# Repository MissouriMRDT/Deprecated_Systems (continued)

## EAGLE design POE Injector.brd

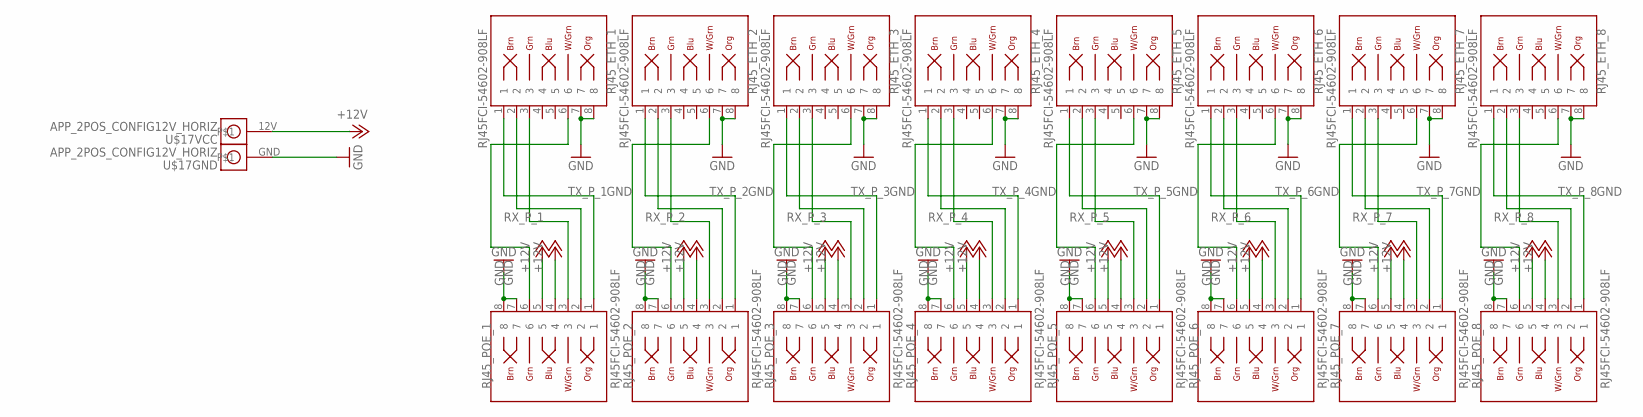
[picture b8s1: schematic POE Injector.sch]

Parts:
RJ45_ETH_1, RJ45_ETH_2, RJ45_ETH_3, RJ45_ETH_4, RJ45_ETH_5, RJ45_ETH_6, RJ45_ETH_7, RJ45_ETH_8, RJ45_POE_1, RJ45_POE_2, RJ45_POE_3, RJ45_POE_4, RJ45_POE_5, RJ45_POE_6, RJ45_POE_7, RJ45_POE_8: RJ45FCI-54602-908LF; FCI-54602-908LF
U$17: APP_2POS_CONFIG12V_HORIZ; APP45_12V_HORIZ_CONFIG

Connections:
+12V: RJ45_POE_1.4, RJ45_POE_1.5, RJ45_POE_2.4, RJ45_POE_2.5, RJ45_POE_3.4, RJ45_POE_3.5, RJ45_POE_4.4, RJ45_POE_4.5, RJ45_POE_5.4, RJ45_POE_5.5, RJ45_POE_6.4, RJ45_POE_6.5, RJ45_POE_7.4, RJ45_POE_7.5, RJ45_POE_8.4, RJ45_POE_8.5, U$17.12V
GND: RJ45_ETH_1.7, RJ45_ETH_1.8, RJ45_ETH_2.7, RJ45_ETH_2.8, RJ45_ETH_3.7, RJ45_ETH_3.8, RJ45_ETH_4.7, RJ45_ETH_4.8, RJ45_ETH_5.7, RJ45_ETH_5.8, RJ45_ETH_6.7, RJ45_ETH_6.8, RJ45_ETH_7.7, RJ45_ETH_7.8, RJ45_ETH_8.7, RJ45_ETH_8.8, RJ45_POE_1.7, RJ45_POE_1.8, RJ45_POE_2.7, RJ45_POE_2.8, RJ45_POE_3.7, RJ45_POE_3.8, RJ45_POE_4.7, RJ45_POE_4.8, RJ45_POE_5.7, RJ45_POE_5.8, RJ45_POE_6.7, RJ45_POE_6.8, RJ45_POE_7.7, RJ45_POE_7.8, RJ45_POE_8.7, RJ45_POE_8.8, U$17.GND
RX_N_1: RJ45_ETH_1.6, RJ45_POE_1.6
RX_N_2: RJ45_ETH_2.6, RJ45_POE_2.6
RX_N_3: RJ45_ETH_3.6, RJ45_POE_3.6
RX_N_4: RJ45_ETH_4.6, RJ45_POE_4.6
RX_N_5: RJ45_ETH_5.6, RJ45_POE_5.6
RX_N_6: RJ45_ETH_6.6, RJ45_POE_6.6
RX_N_7: RJ45_ETH_7.6, RJ45_POE_7.6
RX_N_8: RJ45_ETH_8.6, RJ45_POE_8.6
RX_P_1: RJ45_ETH_1.3, RJ45_POE_1.3
RX_P_2: RJ45_ETH_2.3, RJ45_POE_2.3
RX_P_3: RJ45_ETH_3.3, RJ45_POE_3.3
RX_P_4: RJ45_ETH_4.3, RJ45_POE_4.3
RX_P_5: RJ45_ETH_5.3, RJ45_POE_5.3
RX_P_6: RJ45_ETH_6.3, RJ45_POE_6.3
RX_P_7: RJ45_ETH_7.3, RJ45_POE_7.3
RX_P_8: RJ45_ETH_8.3, RJ45_POE_8.3
TX_N_1: RJ45_ETH_1.2, RJ45_POE_1.2
TX_N_2: RJ45_ETH_2.2, RJ45_POE_2.2
TX_N_3: RJ45_ETH_3.2, RJ45_POE_3.2
TX_N_4: RJ45_ETH_4.2, RJ45_POE_4.2
TX_N_5: RJ45_ETH_5.2, RJ45_POE_5.2
TX_N_6: RJ45_ETH_6.2, RJ45_POE_6.2
TX_N_7: RJ45_ETH_7.2, RJ45_POE_7.2
TX_N_8: RJ45_ETH_8.2, RJ45_POE_8.2
TX_P_1: RJ45_ETH_1.1, RJ45_POE_1.1
TX_P_2: RJ45_ETH_2.1, RJ45_POE_2.1
TX_P_3: RJ45_ETH_3.1, RJ45_POE_3.1
TX_P_4: RJ45_ETH_4.1, RJ45_POE_4.1
TX_P_5: RJ45_ETH_5.1, RJ45_POE_5.1
TX_P_6: RJ45_ETH_6.1, RJ45_POE_6.1
TX_P_7: RJ45_ETH_7.1, RJ45_POE_7.1
TX_P_8: RJ45_ETH_8.1, RJ45_POE_8.1

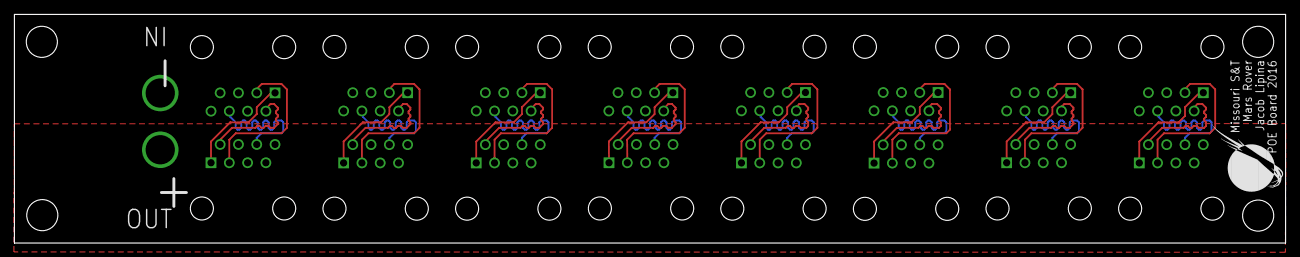
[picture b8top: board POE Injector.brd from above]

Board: 2 copper layers, 176.5 x 31.8 mm, 18 parts (0 on the bottom side), 34 nets.

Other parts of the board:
U$1: MRDT_LOGO

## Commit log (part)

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2016-10-25 Updated Gitignore and removed stray file
2016-10-25 Finished routing Dropbay Connectors
2016-10-27 Code standard changes, more comments.
2016-10-28 Implemented read and graph of spectrometer data.
2016-11-03 Updated template area to latest template
2016-11-04 Added 12V Actuation to run servos
2016-11-04 Updated Donation Address
2016-11-05 Added LSM9DS1 IMU to MRDT-Sensors
2016-11-06 Completed Rev 1 of Science Board
    Added second sensor board and completed board design.
2016-11-06 Rounded corners of board
2016-11-06 Edits after review
    Complete rearrangement of board to put circuitry under Tiva, with
    horizontal connectors. Changed layout of photodiode amplifier circuit to
    reduce noise. Added mounting holes and rounded corners. Replaced I2C
    level shifter IC. tided up traces and component names.
2016-11-07 Stitched GNDs better
2016-11-07 Added SL02-Horiz
2016-11-08 Changed drill size for Vias to 12mil
2016-11-08 Add SL5 connectors for motors, passthrough serial data
    Motors get independent control in normal mode, tank steer (left together, right together) in failover mode
2016-12-03 Converted DropBay control to use an array of Servos
2016-12-16 update gitignore
2016-12-16 Weather and Soil Sensor boards
2017-01-05 Add tab to display pictures
2017-01-07 Added name to test point package
2017-01-08 Finished routing and labeled board
2017-01-10 Updated LXDC2HN
2017-01-12 Completed board review #1 revisions
2017-01-12 Board Review revisions completed
2017-01-21 Add images to directory and add functionality to import png images
2017-01-27 Test app functionality for science board
    Test app to control flap, laser, carousel, other functions. in
    development
2017-02-02 Create show picture funciton
2017-02-03 Updated to match ordered Ext Controls board
    Made Vias Smaller
    Moved Ethernet Circuitry lower
    Added Actuation Bus
    Updated Libraries
    Rounded Board Corners
2017-02-03 Added Max4312 chip to schematic
2017-02-03 Added Molex BNC
2017-02-04 added opamp
2017-02-04 Testing science board things
    minor changes
2017-02-10 Remove arm.h, update science board code
2017-02-15 Added dynamixel connector and serial line
2017-02-25 Orgainize Test Sketches into one folder
2017-03-01 Tested and fixed these sketches.
    I have seen these work!
2017-03-02 added arm board V2's 3.3V lin reg
2017-03-04 Added more comments to improve readability
    Added comments for functions, control blocks, and the mail execution
    loop, Added TODO: coments
2017-03-09 Traces for Dynamixels and extra PWMs
2017-03-14 added arm board inductor
2017-03-15 Make Cmd ID enum, added millis sensor delay
    Enumerated command Data for science commands, added delay between sensor
    reads, initialized all sensors to off
2017-03-18 Switch main motor driver, fixed issues with 3V3
2017-03-20 Integrated weather sensor board, started soil sensor integration, changed spectrometer motor driver
2017-03-21 Quick + basic RPi hat
2017-03-22 some changes from board review
    > remove diodes for LEDs
    > space out FETs
    > separate grounds for FETs
    > Move vias out from under FETs
2017-03-22 Removed unnecessary 3v3 net and swapped header with eagle standard part
2017-03-23 made changes related to board review
2017-03-23 Widened board and spaced out connectors
2017-03-23 Changes to Arm board
    Fixed text, added divider resistors to sensors, added power LED, rearranged schematic slightly
2017-03-23 Added the actual program file for arm
    Added the actual science arm main program
2017-03-23 adjustable regulator for laser
    BA00DD0WHFP-TR
2017-03-23 changed tiva pins for soil sensors
2017-03-23 Rerouted 12V_ACT for better planes
2017-03-23 ONE MORE I SWEAR
    fixed airwire.
2017-03-23 Updated Revision text
2017-03-23 finished gimbal breakout
    added mounting holes
    labeled board
    fixed traces
2017-04-02 Debug Work - flap and serial comm
    switched flap open and close angles
    tweaked flap open and close angles
    commented out annoying print messages
2017-04-03 Basic functionality for soil temperature and humidity readings as well as spectrometer are implemented and elementary test confirmed.
2017-04-04 Four pictures input as a 2x2 grid on the picture tab.
2017-04-05 Small changes
2017-04-05 Dynamixel LED blinking for debugging (untested)
2017-04-06 Modify to account for Gryphon graphs (Gryphs? Graphon?). Untested with real data. Add QOL picture features (fullscreen, browsed file input)
2017-04-06 Both gimbals fully functional
2017-04-09 changes due to new science board
    testing for carousel, new pins
2017-04-13 add this file
    add this file
2017-04-22 fixed main gimabal serial, and added untested menu functionality
2017-04-22 Code Review 2, Updated TODOs
    Second Code Review, 4/22/17, Updated TODOs in arm board and science
    board
2017-04-23 adding sensor code to science and sci-arm
    copied code from sensor test sketches into science.ino and arm.ino/arm.h
    init all sensor pins for input
    set sensor pins in header file
2017-04-28 added sensor functions to arm board and clean up science.ino
    add ability for continuous data to science arm board, clean up
    code/better organize it ☺
2017-04-29 added AZ1117EH-5.0
2017-05-09 Defined Pins, Added Config, Matched CommandIDs
    Defined Pins in header files, Added Configuration File for Future Sensor
    Calibration, Matched Command IDs to the current RED version
2017-05-15 TCP for phot data and data ids for arm
    :+1:
2017-05-23 updated parameters and tested sample data
2017-05-23 Added Drop Bay close capability
2017-05-24 Added end of year stuff and fixed change to sensor names
2017-05-25 updated carabiner code
2017-05-26 Started implementing new data processing method
2017-05-26 plotted spectrometer data
2017-05-26 Corrected diode switch
2017-05-27 Fixed carabiner value check
2017-09-12 Pre-repo progress commit
2017-09-14 Spectra should be working properly.
2017-09-15 Requests for weather, soil, spectrometer, all working.
2017-09-23 Add functionality to insert raw spectra
2017-09-23 Subscribe to all IP addresses from our configuration file
2017-09-24 Finished adding comps and changing labels
    All components that will be on gimbal pwer board have been added and wires have been renamed to match gimbal design. Last schematic change to make is label header pins.
2017-09-28 Upgrade from PyQt4 to PyQt5.
2017-09-29 Added the 74LVC 2-1 Demux
    Added 2-1 demux and fixed some of the packages added in previous commit
    (added pin 1 markers).
2017-10-01 Added grounds for the acs781
2017-10-01 specroprocessing
2017-10-01 Header pins to control card named
    All traces that will go to control card have been named on a header pin and can be rearanged for more convienent layout. Power indication simplified.
2017-10-01 C2000 Launchpad Schematic and Board
    C2000 CAD files
2017-10-08 Deleted accidental Eagle files
2017-10-13 The motor controller driver for powerboard is ready for rev 1
    This is the complete powerboard design based off of what was decided at the Gimbal meetings. The actual schematic for the board is simply 1A.sch and the board design is 1A.brd I did change some pin a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
2017-10-15 Capacitor fixed
    Hole outline was on the wrong layer
2017-10-16 Started deleting unnecessary hardware on F28069M
    Matched pinout from 28027F with pins on 28069M and deleted all remeaining unnecessary pins. Deleted the debugging and flashing hardware. Decided to delete all muxes and logic gates because we believe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
2017-10-19 Added F28069M Microcontroller
    Took Ti's schematic and board and deleted unecessary functionality. We are using what remains as an integrated version of the F28069M.
2017-10-19 Deleted lock
    My eagle keeps adding locks to my files, which may prevent other people from opening the files, I'm not really sure.
2017-10-20 Named GPIO and ADC pins on F28069M
    Still need to sort out errors identified by ERC.
2017-10-21 Removed Temp Files
2017-10-21 Rearanged Board and rounded edges
    Put Anderson Connectors in correct places as well as rewired the whole board. I then rounded the corners of the board and put wholes in the board so we could properly mount it. Eagle would not allow 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
2017-10-28 Initialize subscriber array with null ip addresses / data id's
2017-10-29 Got width standardized
    Every wire and polygon now has a width of 16 mil
2017-10-29 Fets are now foldable
    Had to move caps around to get fets ample space to be able to be folded down under the board. Approximately 20mm of space. Will still need changes as top chip is finished. Power now has to round seve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
2017-10-30 layout for control card created
    Placed large components, now placing placing passive components individually and routing
2017-11-02 Quick Routing and Labeling Fix
    Straigtenned header names and made sure polygons stretched to same length on board.
2017-11-04 Added Silkscreen and Bill of Materials
    Bill of materials is now added and can be changed as time goes on. All objects on board have been smashed and names are fairly visible. Some areas around phase C are hard to read due to spacing. Silk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
2017-11-04 Fixed some spacing issues
    Moved a wire and straigtenned some polygons for a tighter board.
2017-11-04 more finishing touches.
2017-11-06 Deleted brd and edited schematic
2017-11-07 finsihed simple connections. All devices are on board. Still a lot of pins on header that need to be connected to microprocessor. A lot of them cross. Not sure if possible without vias.
2017-11-08 All the routing is finished. It needs some serious cleaning up and there are most likely mistakes.
2017-11-14 Added BOM and order sheet, modified Board Layout
2017-11-14 Updated Gerber Files; Final changes to board design
2017-11-16 Drill Board: Starting from a clean slate (power and filtering only)
2017-12-02 Fixed formatting for google doc initial push.
2017-12-02 Made data, data_byte_count, and data_id zero in Rovecomm_recieve. UNTESTED
2017-12-09 Fixed some naming errors and moved all funcions out of _init_
2017-12-09 Make Readme formatting nicer
2017-12-30 Added SL connectors & MAX232, added Andrew's JTAG connector
    Added SL connectors from gimbal power board and added connections to BOOSTXL header / MAX232. Same implementation as gimbal power board.
2018-01-01 Improved Interface Documentation
2018-01-04 Finished Routing Board
    Board is finished with routing, however it needs silkscreen to be done. Silk screen will be completed at a later date. There is one unbroken ground plain. Top plain is fairly broken as a ground plane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
2018-01-14 Remved unnecesary files
    BOM and connection information moved to Google Drive under 2018-->Rovecore Electrical-->Programmer Board
2018-01-15 Updated silkscreen and moved reset switch
    The board was shrunken for better fitting with boards that this card will be compatible with. Reset switch was moved to accomodate this. The Jtag connector routing was fixed due to a placement error.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
2018-01-20 Did a little comment reformatting
2018-01-20 first training
2018-01-23 Routing and Silkscreen Update
    New routes were made and Silkscreen changes were made. SL connectors are now labelled and arrows indicate direction of headers.
2018-01-24 Updated schematic and board for final board review
    Changed oscilator for ATMEGA
    changed power to ATMEGA to 3.3V
    Cleaned up position and traces
    Added mounting holes
    Added signature and board data
2018-01-24 Removed redundant SL connector, restructured right side of board and reduced board size
2018-01-25 Rev 3 Gerbs created
2018-01-25 Control Card Routing Update
    Connected VCC to all necessary parts.
2018-01-27 Routing Update
    Board's routing was completely redone and is much more efficient with plenty of vias connecting the ground planes.
2018-01-28 Small Via changes
2018-01-31 Created Gerbs
2018-02-04 Updated read me
2018-02-04 readme
2018-02-04 Master read me
2018-02-04 Revert "Added JLCPCB CAM files"
    This reverts commit 26ec2af4e529b2b3f0f422ca2c6a6f543a598df3.
2018-02-10 Fixed spelling of receiveFrom()
2018-02-11 recv_header=True for rove db on recvFrom
2018-02-18 Finished Board Wiring
2018-02-24 Modified board
2018-03-11 Added Schematic and Layout
2018-03-12 Added PWM Output on Headers as backup if serial does not work.
2018-03-17 Made naming changes that may mess things up...
    renamed all components with dashes to us underscores
2018-03-19 Removed Report
2018-04-01 sorting for archiving
2018-04-02 restructuring for archiving
2018-04-21 began to match this year's pins
